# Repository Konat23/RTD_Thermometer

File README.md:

# RTD_Thermometer
A system that allows to measure and visualize the temperature using a thermal resistance sensor (RTD). The system was designed to measure temperatures between 0°C and 100°C with a precision of 0.1°C

## Team members
- Juan Sebastian Guerrero Peña

- Sebastian Garcia Angarita

- Juliana Lucía Pineda Cardozo 

- Laura Sofía Valero García

## Summary of Results
### Hardware design (PCB assembly)

### Software design (User Interface)

### System in operation results

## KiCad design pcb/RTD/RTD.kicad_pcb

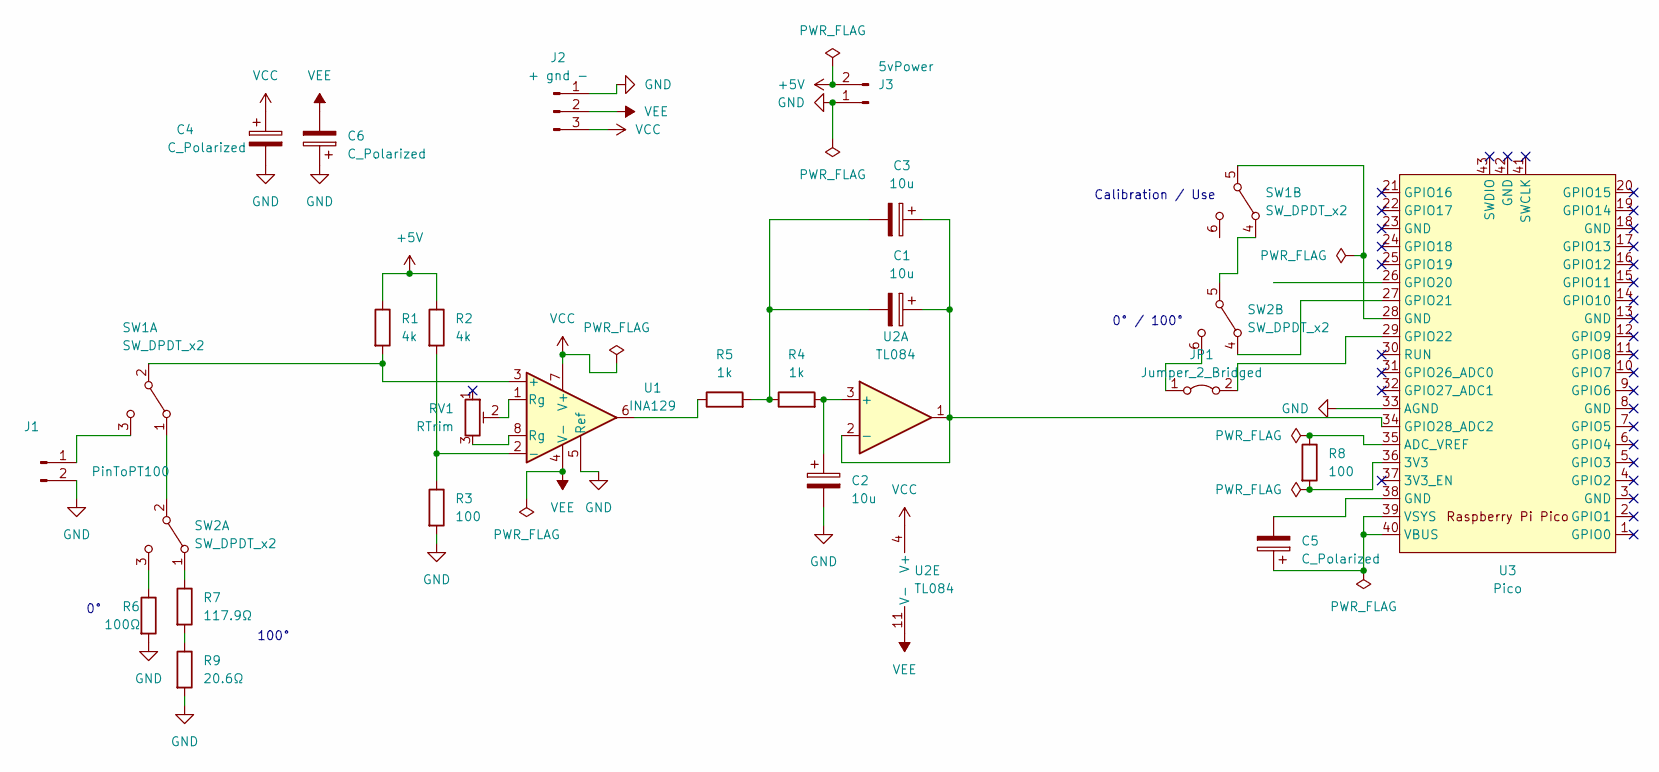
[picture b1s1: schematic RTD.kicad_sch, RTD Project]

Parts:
C1, C2, C3: 10u; CP_Radial_D5.0mm_P2.50mm
C4, C5, C6: C_Polarized; CP_Radial_D5.0mm_P2.50mm
J1: PinToPT100; TerminalBlock_bornier-2_P5.08mm
J2: + gnd -; TerminalBlock_bornier-3_P5.08mm
J3: 5vPower; TerminalBlock_bornier-2_P5.08mm
JP1: Jumper_2_Bridged; jumper-wire_8mm
R1, R2: 4k; R_Axial_DIN0411_L9.9mm_D3.6mm_P12.70mm_Horizontal
R3: 100; R_Axial_DIN0411_L9.9mm_D3.6mm_P12.70mm_Horizontal
R4, R5: 1k; R_Axial_DIN0411_L9.9mm_D3.6mm_P12.70mm_Horizontal
R6: 100Ω; R_Axial_DIN0411_L9.9mm_D3.6mm_P12.70mm_Horizontal
R7: 117.9Ω; R_Axial_DIN0411_L9.9mm_D3.6mm_P12.70mm_Horizontal
R8: 100; R_Axial_DIN0309_L9.0mm_D3.2mm_P2.54mm_Vertical
R9: 20.6Ω; R_Axial_DIN0411_L9.9mm_D3.6mm_P12.70mm_Horizontal
RV1: RTrim; Potentiometer_Bourns_3386C_Horizontal
SW1, SW2: SW_DPDT_x2; DIP-Switch-2P2T
U1: INA129; DIP254P762X508-8
U2: TL084; DIP794W45P254L1969H508Q14
U3: Pico; RPi_Pico_SMD_TH

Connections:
+5V: J3.2, R1.1, R2.1
GND: C2.2, C4.2, C6.1, J1.2, J2.1, J3.1, R3.2, R6.2, R9.2, U1.5 (Ref), U3.33 (AGND)
unnamed: C1.2, C3.2, R4.1, R5.2
unnamed: C5.2, U3.38 (GND)
unnamed: J1.1, SW1.3 (C)
unnamed: JP1.1 (A), SW2.6 (C)
unnamed: JP1.2 (B), U3.29 (GPIO22)
unnamed: R5.1, U1.6
unnamed: R7.2, R9.1
unnamed: RV1.2, U1.1 (Rg)
unnamed: RV1.3, U1.8 (Rg)
unnamed: SW1.1 (A), SW2.2 (B)
unnamed: R1.2, SW1.2 (B), U1.3 (+)
unnamed: SW1.4 (A), SW2.5 (B)
unnamed: SW1.5 (B), U3.28 (GND)
unnamed: R7.1, SW2.1 (A)
unnamed: R6.1, SW2.3 (C)
unnamed: SW2.4 (A), U3.27 (GPIO21)
unnamed: R2.2, R3.1, U1.2 (-)
unnamed: C2.1, R4.2, U2.3 (+)
unnamed: C1.1, C3.1, U2.1, U2.2 (-), U3.34 (GPIO28_ADC2)
unnamed: R8.2, U3.36 (3V3)
unnamed: R8.1, U3.35 (ADC_VREF)
unnamed: C5.1, U3.39 (VSYS), U3.40 (VBUS)
VCC: C4.1, J2.3, U1.7 (V+), U2.4 (V+)
VEE: C6.2, J2.2, U1.4 (V-), U2.11 (V-)

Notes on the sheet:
0° / 100°
100°
Calibration / Use

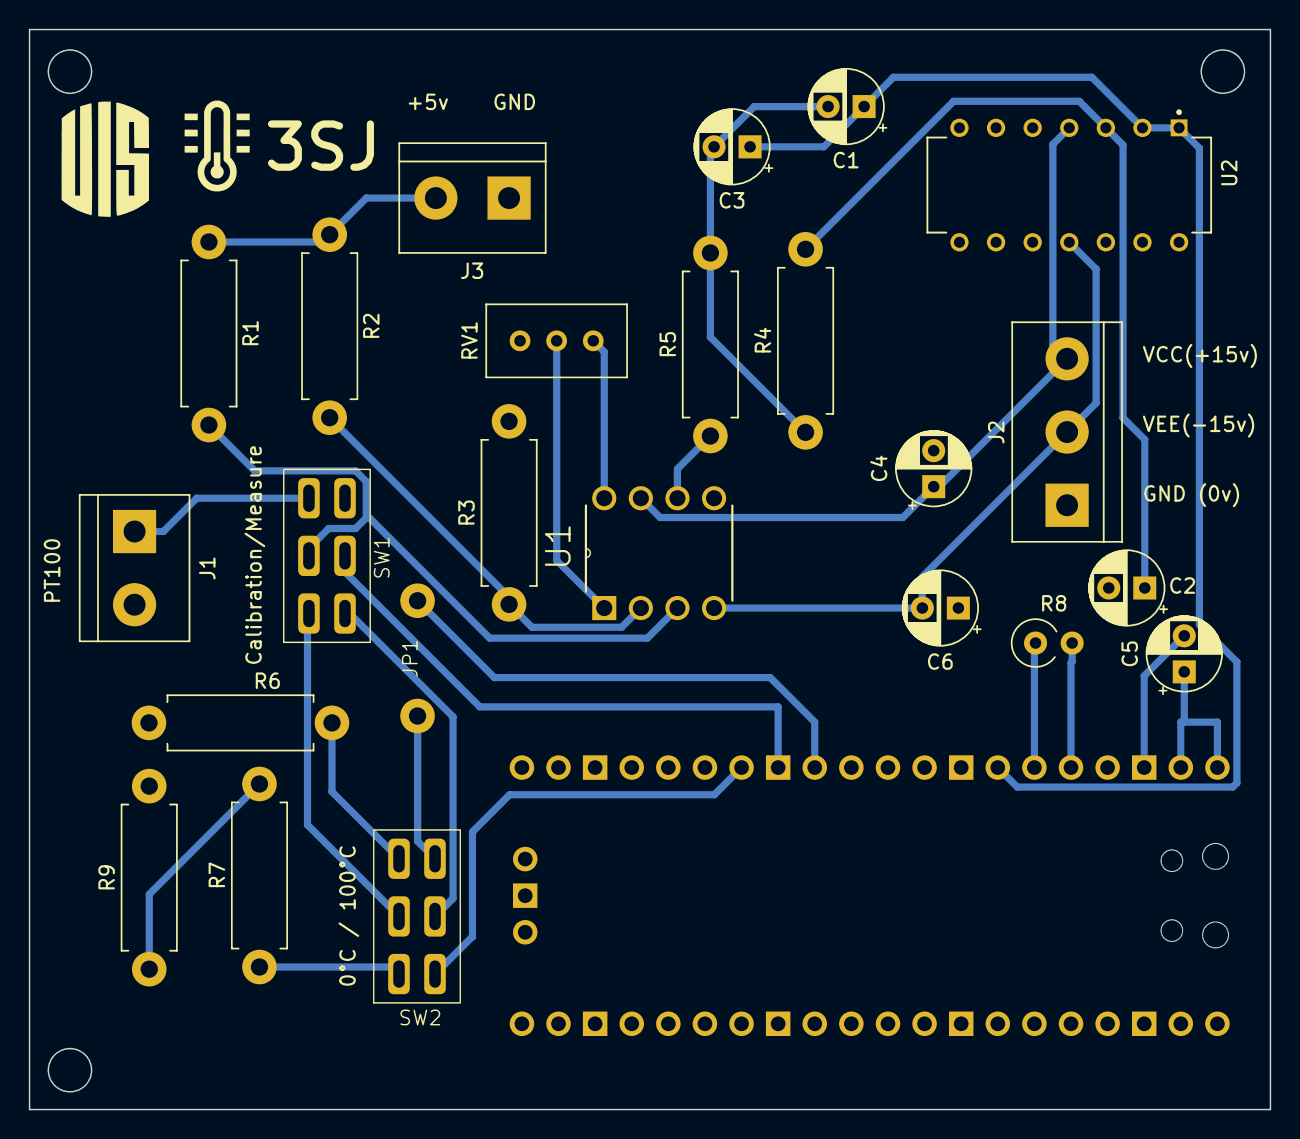
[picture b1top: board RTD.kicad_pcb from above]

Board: 2 copper layers, 86.1 x 74.9 mm, 25 parts (1 on the bottom side), 26 nets.

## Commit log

2023-10-29 added submodule and report
2023-10-29 added pcb files
2023-10-29 added other docs files
